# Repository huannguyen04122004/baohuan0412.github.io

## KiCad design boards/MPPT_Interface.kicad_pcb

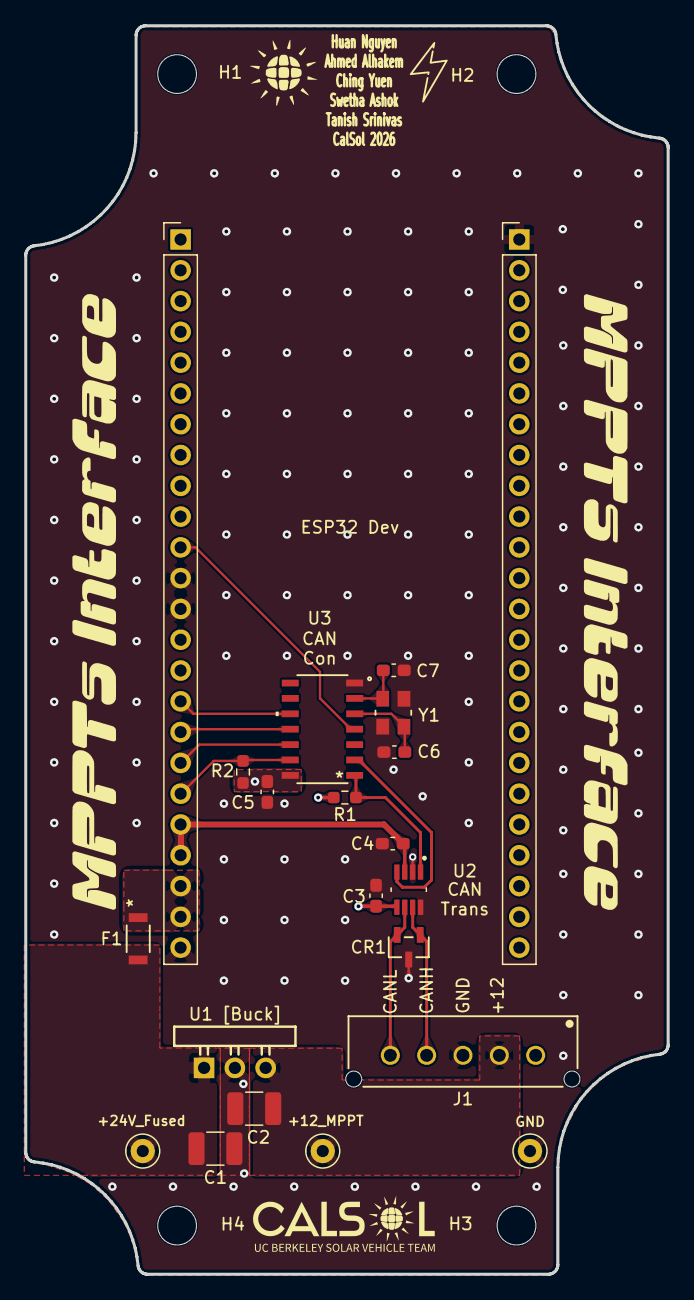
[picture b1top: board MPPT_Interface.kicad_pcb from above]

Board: 4 copper layers, 53.0 x 103.0 mm, 24 parts (0 on the bottom side), 17 nets.

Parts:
+12_MPPT, +24V_Fused: TestPoint; TestPoint_Keystone_5000-5004_Miniature
C1: 10μF; C_1210_3225Metric_Pad1.33x2.70mm_HandSolder
C2: 47μF; C_1210_3225Metric_Pad1.33x2.70mm_HandSolder
C3, C4, C5: 100nF; C_0603_1608Metric_Pad1.08x0.95mm_HandSolder
C6, C7: 18pF; C_0603_1608Metric_Pad1.08x0.95mm_HandSolder
CR1: ESD2CAN36DBZRQ1; SOT-23-3_DBZ_TEX
ESP32 Dev: ESP32 Dev Board V3; ESP32v3
F1: 0466001.NR; 0466Series_LTF
GND: TestPoint; TestPoint_Keystone_5000-5004_Miniature
H1, H2, H3, H4: MountingHole; MountingHole_3.2mm_M3
J1: 436500529; CONN_SD-43650-010_05_MOL
R1: 5.1kΩ; R_0603_1608Metric_Pad0.98x0.95mm_HandSolder
R2: 10kΩ; R_0603_1608Metric_Pad0.98x0.95mm_HandSolder
U1 [Buck]: TPSM84212EAB; EAB0003A
U2: TCAN1472VDDFRQ1; SOT65P280X110-8N
U3: MCP2518FDT-E/SL; SOIC14_SL_MCH
Y1: ABM8G-40.000MHZ-18-D2Y-T; CRYSTAL_ABM8G_ABR

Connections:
+3.3V: C3.1, C5.1, ESP32 Dev.1 (+3.3V), ESP32 Dev.48 (+3.3V), R1.1, R2.1, U2.5 (VIO), U3.14 (VDD)
+5V: C4.1, ESP32 Dev.20 (+5V), ESP32 Dev.21 (+5V), U2.3 (VCC)
+24V: ESP32 Dev.22 (+24V_Out), ESP32 Dev.23 (+24V_Out), F1.1
/+12_MPPT: +12_MPPT.1 (1_1), C2.1, J1.2, U1 [Buck].3 (VOUT)
/+24V_FUSED: +24V_Fused.1 (1_1), C1.1, F1.2, U1 [Buck].1 (VIN)
/MPPT_CANH: CR1.1 (IO), J1.4, U2.7 (CANH)
/MPPT_CANL: CR1.2 (IO), J1.5, U2.6 (CANL)
/MPPT_CAN_INT: ESP32 Dev.11 (IO8), U3.4 (*INT)
/MPPT_CAN_RX: U2.4 (RXD), U3.2 (RXCAN)
/MPPT_CAN_TX: R1.2, U2.1 (TXD), U3.1 (TXCAN)
/MPPT_SPI_CS: ESP32 Dev.19 (IO12), R2.2, U3.13 (nCS)
/MPPT_SPI_MISO: ESP32 Dev.18 (IO11), U3.12 (SDO)
/MPPT_SPI_MOSI: ESP32 Dev.17 (IO10), U3.11 (SDI)
/MPPT_SPI_SCK: ESP32 Dev.16 (IO9), U3.10 (SCK)
GND: C1.2, C2.2, C3.2, C4.2, C5.2, C6.2, C7.2, CR1.3 (GND), ESP32 Dev.12 (GND), ESP32 Dev.13 (GND), ESP32 Dev.24 (GND), ESP32 Dev.25 (GND), GND.1 (1_1), J1.3, U1 [Buck].2 (GND), U2.2 (GND), U2.8 (STB), U3.7 (VSS), Y1.2 (GND), Y1.4 (GND)
unnamed: C7.1, U3.6 (OSC1), Y1.1
unnamed: C6.1, U3.5 (OSC2), Y1.3
